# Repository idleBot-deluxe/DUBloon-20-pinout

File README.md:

# DUBloon-20-pinout
This pcb organizes controller pad signals to easily interface with the Brook 20-pin wire harness allowing for fast swaps between consoles / controllers.

BOM:
2.54" 2x10 straight pin header male

(Wii U Afterglow 3rd party controller)

(Gutted SF TE stick)

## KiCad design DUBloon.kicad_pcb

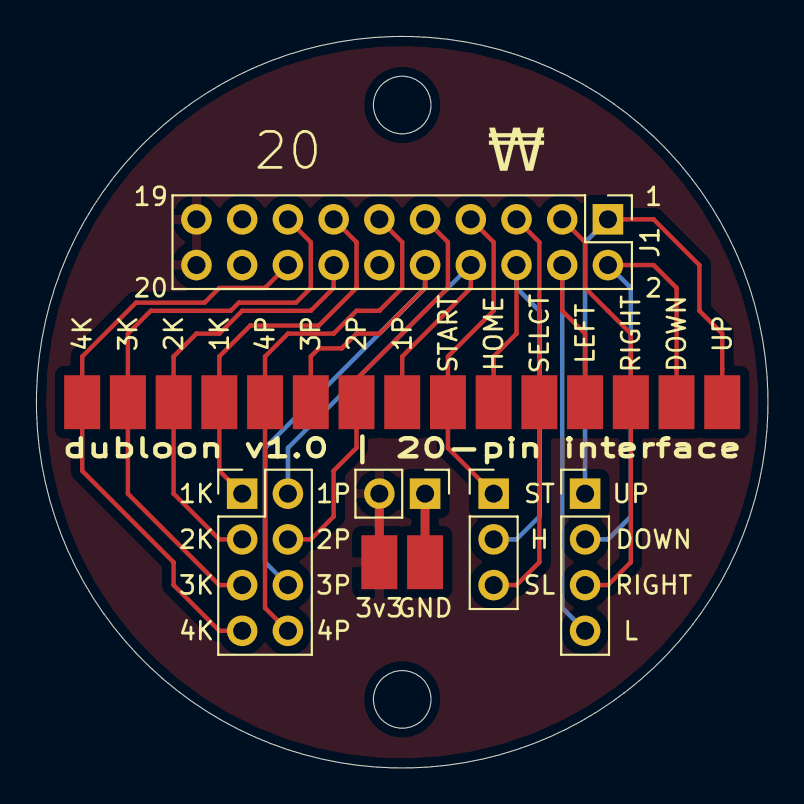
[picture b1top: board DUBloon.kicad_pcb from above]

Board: 2 copper layers, 40.6 x 40.6 mm, 6 parts (0 on the bottom side), 9 nets.

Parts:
3v3: solderPad2x3mm
Directions: Pin_Header_Straight_1x04_Pitch2.54mm
GND: solderPad2x3mm
J1: 20-Pin Connector; Pin_Header_Straight_2x10_Pitch2.54mm
MNU: Pin_Header_Straight_1x03_Pitch2.54mm
PWR: Pin_Header_Straight_1x02_Pitch2.54mm

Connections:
+3V3: 3v3.1, J1.19, J1.20, PWR.2
DOWN: Directions.2, J1.2
GND: GND.1, J1.12, J1.17, J1.18, PWR.1
HOME: J1.6, MNU.2
LEFT: Directions.4, J1.4
RIGHT: Directions.3, J1.3
SELECT: J1.5, MNU.3
START: J1.7, MNU.1
UP: Directions.1, J1.1

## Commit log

2022-05-14 Create LICENSE
